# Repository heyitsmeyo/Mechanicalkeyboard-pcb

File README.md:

# Mechanicalkeyboard-pcb
a pcb design for a mechanical keyboard based on RP2040 MCU 

# if you like the project , you can donate us for more : 

    https://ko-fi.com/heyitsmeyo

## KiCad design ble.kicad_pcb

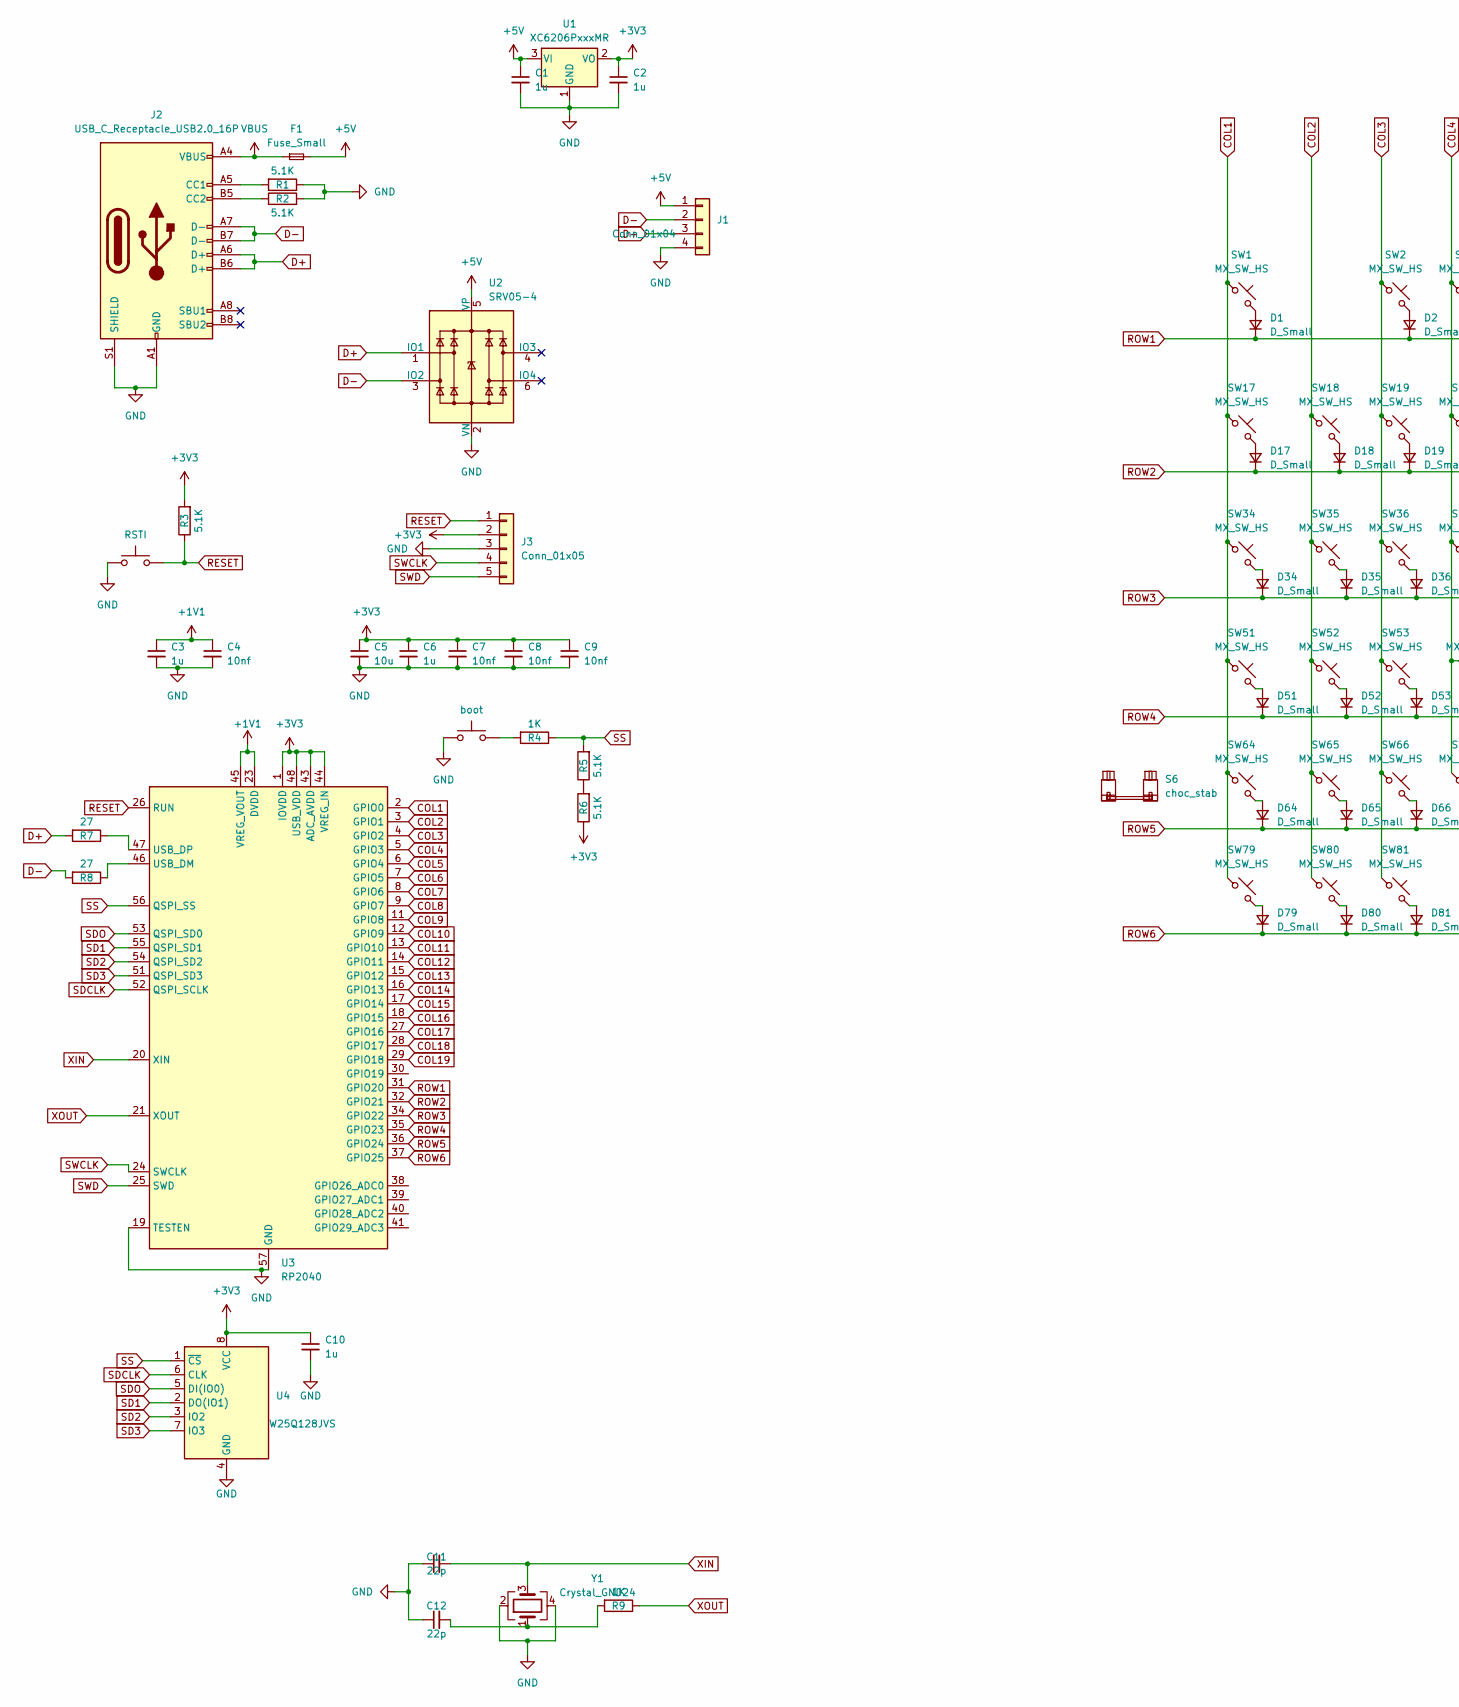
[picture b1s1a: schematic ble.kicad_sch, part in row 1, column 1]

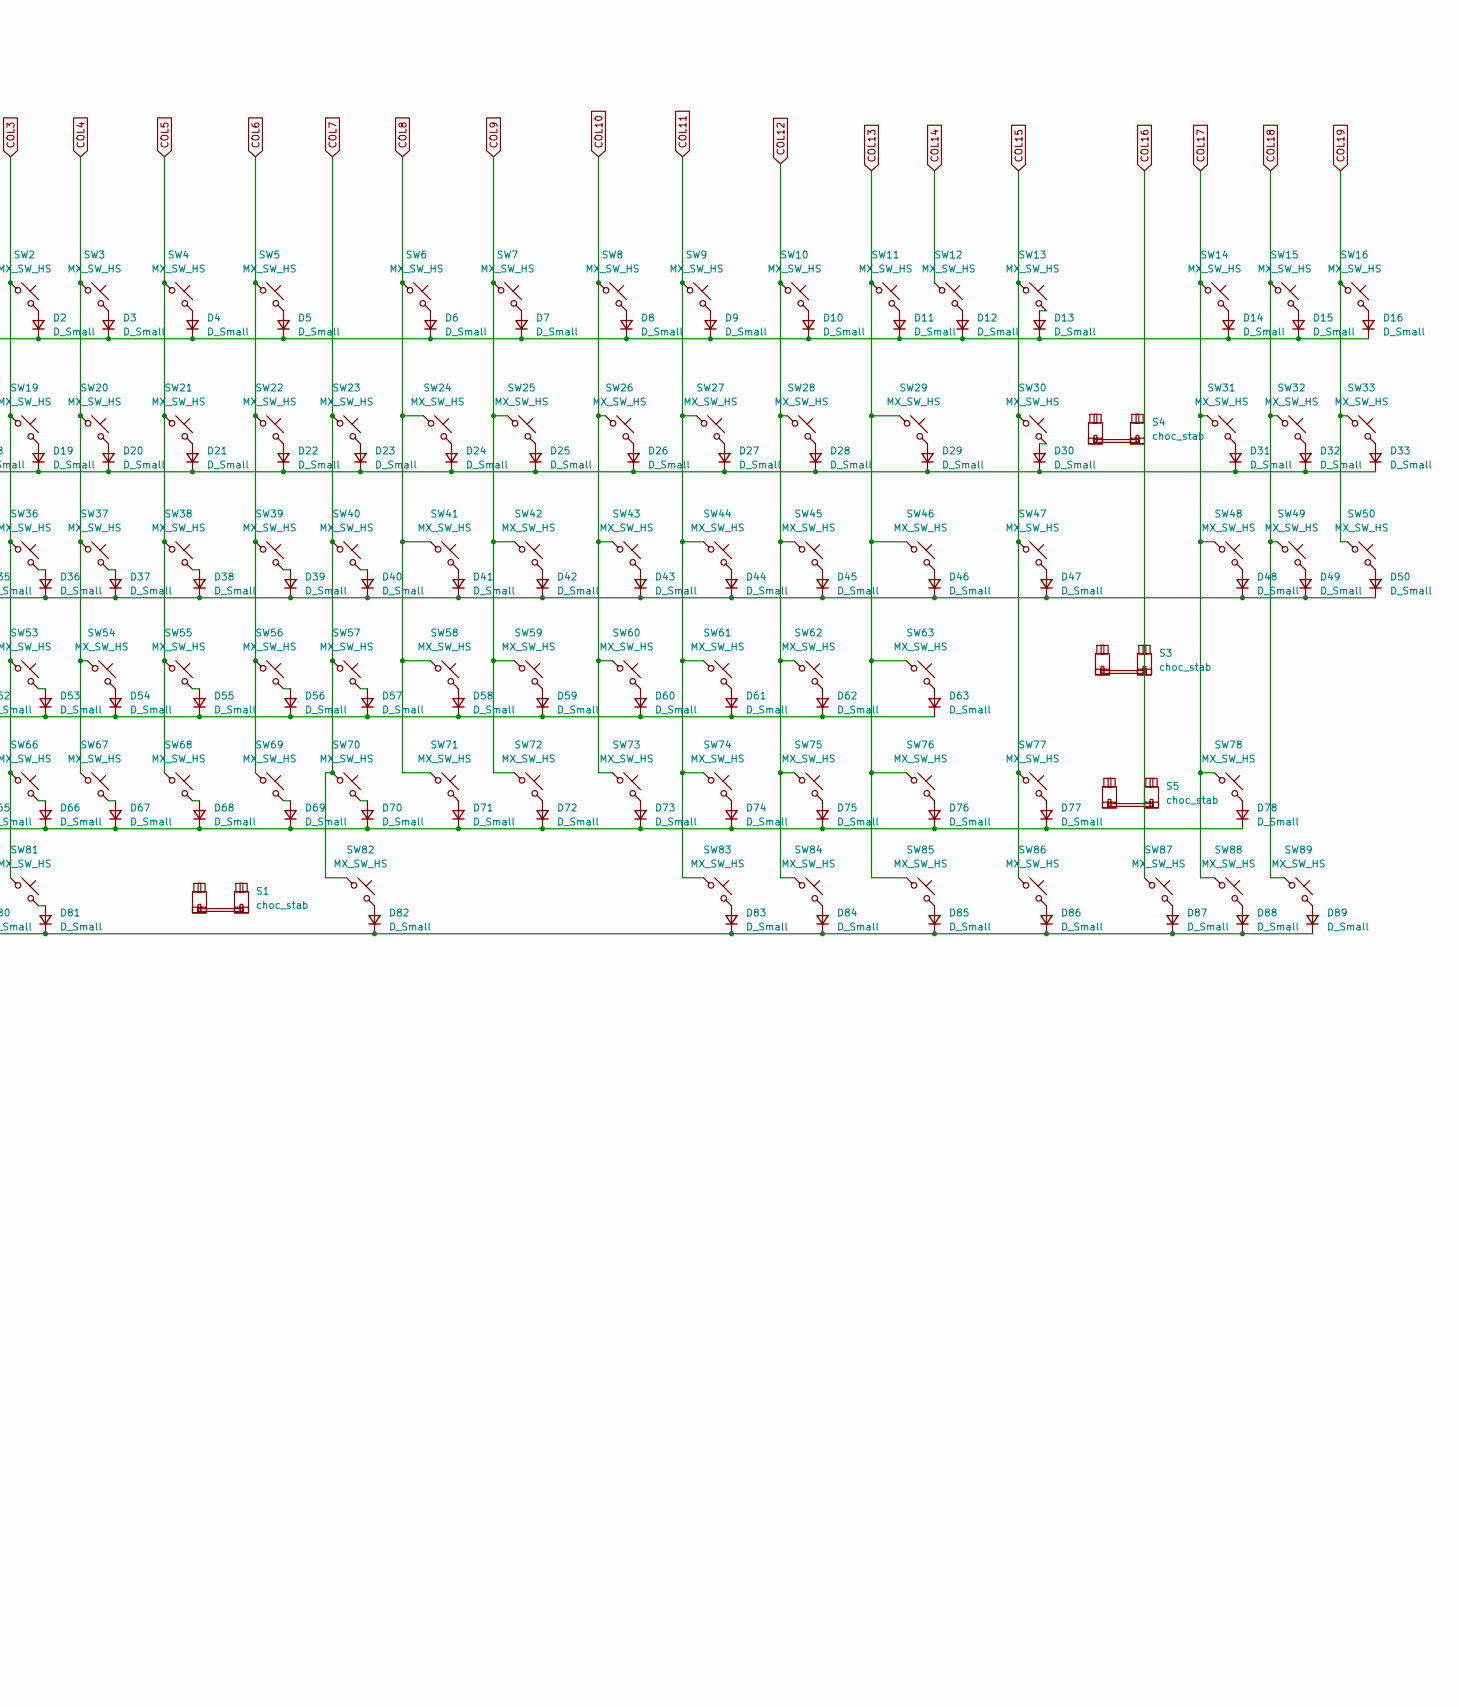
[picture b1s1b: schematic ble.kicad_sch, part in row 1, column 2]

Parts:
C1, C2, C3, C6, C10: 1u; C_0402_1005Metric
C4, C7, C8, C9: 10nf; C_0402_1005Metric
C5: 10u; C_0603_1608Metric
C11, C12: 22p; C_0402_1005Metric
D1, D2, D3, D4, D5, D6, D7, D8, D9, D10, D11, D12, D13, D14, D15, D16, D17, D18, D19, D20, D21, D22, D23, D24, D25, D26, D27, D28, D29, D30, D31, D32, D33, D34, D35, D36, D37, D38, D39, D40, D41, D42, D43, D44, D45, D46, D47, D48, D49, D50, D51, D52, D53, D54, D55, D56, D57, D58, D59, D60, D61, D62, D63, D64, D65, D66, D67, D68, D69, D70, D71, D72, D73, D74, D75, D76, D77, D78, D79, D80, D81, D82, D83, D84, D85, D86, D87, D88, D89: D_Small; D_SOD-123
F1: Fuse_Small; Fuse_1206_3216Metric
J1: Conn_01x04; JST_SH_SM04B-SRSS-TB_1x04-1MP_P1.00mm_Horizontal
J2: USB_C_Receptacle_USB2.0_16P; USB_C_Receptacle_HRO_TYPE-C-31-M-12
J3: Conn_01x05; PinHeader_1x05_P2.54mm_Vertical
R1, R2, R3, R5, R6: 5.1K; R_0402_1005Metric
R4, R9: 1K; R_0402_1005Metric
R7, R8: 27; R_0402_1005Metric
S1: choc_stab; STAB_MX_7u
S3: choc_stab; STAB_MX_ISO-ROT
S4, S6: choc_stab; STAB_choc_2u
S5: choc_stab; STAB_MX_2.25u
SW1, SW2, SW3, SW4, SW5, SW6, SW7, SW8, SW9, SW10, SW11, SW12, SW13, SW14, SW15, SW16, SW17, SW18, SW19, SW20, SW21, SW22, SW23, SW24, SW25, SW26, SW27, SW28, SW29, SW31, SW32, SW33, SW35, SW36, SW37, SW38, SW39, SW40, SW41, SW42, SW43, SW44, SW45, SW46, SW47, SW48, SW49, SW50, SW52, SW53, SW54, SW55, SW56, SW57, SW58, SW59, SW60, SW61, SW62, SW63, SW65, SW66, SW67, SW68, SW69, SW70, SW71, SW72, SW73, SW74, SW75, SW76, SW77, SW78, SW82, SW87: MX_SW_HS; SW_MX_HS_CPG151101S11_1u
SW30, SW34: MX_SW_HS; SW_MX_HS_CPG151101S11_1.5u
SW51: MX_SW_HS; SW_MX_HS_CPG151101S11_1.75u
SW64, SW79, SW80, SW81, SW83, SW84, SW85, SW86, SW88, SW89: MX_SW_HS; SW_MX_HS_CPG151101S11_1.25u
U1: XC6206PxxxMR; SOT-23-3
U2: SRV05-4; SOT-23-6
U3: RP2040; QFN-56-1EP_7x7mm_P0.4mm_EP3.2x3.2mm
U4: W25Q128JVS; SOIC-8_5.23x5.23mm_P1.27mm
Y1: Crystal_GND24; Crystal_SMD_3225-4Pin_3.2x2.5mm
k1: RSTI; SW_SPST_TL3342
k2: boot; SW_SPST_TL3342

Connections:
+1V1: C3.1, C4.1, U3.23 (DVDD), U3.45 (VREG_VOUT), U3.50 (DVDD)
+3V3: C2.1, C5.1, C6.1, C7.1, C8.1, C9.1, C10.1, J3.2, R3.2, R6.1, U1.2 (VO), U3.1 (IOVDD), U3.10 (IOVDD), U3.22 (IOVDD), U3.33 (IOVDD), U3.42 (IOVDD), U3.43 (ADC_AVDD), U3.44 (VREG_IN), U3.48 (USB_VDD), U3.49 (IOVDD), U4.8 (VCC)
+5V: C1.1, F1.2, J1.1, U1.3 (VI), U2.5 (VP)
COL4: SW3.1, SW20.1, SW37.1, SW54.1, SW67.1, U3.5 (GPIO3)
COL5: SW4.1, SW21.1, SW38.1, SW55.1, SW68.1, U3.6 (GPIO4)
COL6: SW5.1, SW22.1, SW39.1, SW56.1, SW69.1, U3.7 (GPIO5)
COL7: SW23.1, SW40.1, SW57.1, SW70.1, SW82.1, U3.8 (GPIO6)
COL8: SW6.1, SW24.1, SW41.1, SW58.1, SW71.1, U3.9 (GPIO7)
COL9: SW7.1, SW25.1, SW42.1, SW59.1, SW72.1, U3.11 (GPIO8)
COL10: SW8.1, SW26.1, SW43.1, SW60.1, SW73.1, U3.12 (GPIO9)
COL11: SW9.1, SW27.1, SW44.1, SW61.1, SW74.1, SW83.1, U3.13 (GPIO10)
COL12: SW10.1, SW28.1, SW45.1, SW62.1, SW75.1, SW84.1, U3.14 (GPIO11)
COL14: SW12.1, U3.16 (GPIO13)
COL15: SW13.1, SW30.1, SW47.1, SW77.1, SW86.1, U3.17 (GPIO14)
COL16: SW87.1, U3.18 (GPIO15)
COL17: SW14.1, SW31.1, SW48.1, SW78.1, SW88.1, U3.27 (GPIO16)
COL19: SW16.1, SW33.1, SW50.1, U3.29 (GPIO18)
D+: J1.3, J2.A6 (D+), J2.B6 (D+), R7.2, U2.1 (IO1)
D-: J1.2, J2.A7 (D-), J2.B7 (D-), R8.2, U2.3 (IO2)
GND: C1.2, C2.2, C3.2, C4.2, C5.2, C6.2, C7.2, C8.2, C9.2, C10.2, C11.1, C12.1, J1.4, J2.A1 (GND), J2.A12 (GND), J2.B1 (GND), J2.B12 (GND), J2.S1 (SHIELD), J3.3, R1.1, R2.2, U1.1 (GND), U2.2 (VN), U3.19 (TESTEN), U3.57 (GND), U4.4 (GND), Y1.2, Y1.4, k1.1, k2.1
unnamed: C12.2, R9.2, Y1.1
unnamed: D1.2 (A), SW1.2
unnamed: D2.2 (A), SW2.2
unnamed: D3.2 (A), SW3.2
unnamed: D4.2 (A), SW4.2
unnamed: D5.2 (A), SW5.2
unnamed: D6.2 (A), SW6.2
unnamed: D7.2 (A), SW7.2
unnamed: D8.2 (A), SW8.2
unnamed: D9.2 (A), SW9.2
unnamed: D10.2 (A), SW10.2
unnamed: D11.2 (A), SW11.2
unnamed: D12.2 (A), SW12.2
unnamed: D13.2 (A), SW13.2
unnamed: D14.2 (A), SW14.2
unnamed: D15.2 (A), SW15.2
unnamed: D16.2 (A), SW16.2
unnamed: D17.2 (A), SW17.2
unnamed: D18.2 (A), SW18.2
unnamed: D19.2 (A), SW19.2
unnamed: D20.2 (A), SW20.2
unnamed: D21.2 (A), SW21.2
unnamed: D22.2 (A), SW22.2
unnamed: D23.2 (A), SW23.2
unnamed: D24.2 (A), SW24.2
unnamed: D25.2 (A), SW25.2
unnamed: D26.2 (A), SW26.2
unnamed: D27.2 (A), SW27.2
unnamed: D28.2 (A), SW28.2
unnamed: D29.2 (A), SW29.2
unnamed: D30.2 (A), SW30.2
unnamed: D31.2 (A), SW31.2
unnamed: D32.2 (A), SW32.2
unnamed: D33.2 (A), SW33.2
unnamed: D34.2 (A), SW34.2
unnamed: D35.2 (A), SW35.2
unnamed: D36.2 (A), SW36.2
unnamed: D37.2 (A), SW37.2
unnamed: D38.2 (A), SW38.2
unnamed: D39.2 (A), SW39.2
unnamed: D40.2 (A), SW40.2
unnamed: D41.2 (A), SW41.2
unnamed: D42.2 (A), SW42.2
unnamed: D43.2 (A), SW43.2
unnamed: D44.2 (A), SW44.2
unnamed: D45.2 (A), SW45.2
unnamed: D46.2 (A), SW46.2
unnamed: D47.2 (A), SW47.2
unnamed: D48.2 (A), SW48.2
unnamed: D49.2 (A), SW49.2
unnamed: D50.2 (A), SW50.2
unnamed: D51.2 (A), SW51.2
unnamed: D52.2 (A), SW52.2
unnamed: D53.2 (A), SW53.2
unnamed: D54.2 (A), SW54.2
unnamed: D55.2 (A), SW55.2
unnamed: D56.2 (A), SW56.2
unnamed: D57.2 (A), SW57.2
unnamed: D58.2 (A), SW58.2
unnamed: D59.2 (A), SW59.2
unnamed: D60.2 (A), SW60.2
unnamed: D61.2 (A), SW61.2
unnamed: D62.2 (A), SW62.2
unnamed: D63.2 (A), SW63.2
unnamed: D64.2 (A), SW64.2
unnamed: D65.2 (A), SW65.2
unnamed: D66.2 (A), SW66.2
unnamed: D67.2 (A), SW67.2
unnamed: D68.2 (A), SW68.2
unnamed: D69.2 (A), SW69.2
unnamed: D70.2 (A), SW70.2
unnamed: D71.2 (A), SW71.2
unnamed: D72.2 (A), SW72.2
unnamed: D73.2 (A), SW73.2
unnamed: D74.2 (A), SW74.2
unnamed: D75.2 (A), SW75.2
unnamed: D76.2 (A), SW76.2
unnamed: D77.2 (A), SW77.2
unnamed: D78.2 (A), SW78.2
unnamed: D79.2 (A), SW79.2
unnamed: D80.2 (A), SW80.2
unnamed: D81.2 (A), SW81.2
unnamed 102: D82.2 (A), SW82.2; also elsewhere on the board
unnamed: D83.2 (A), SW83.2
unnamed: D84.2 (A), SW84.2
unnamed: D85.2 (A), SW85.2
unnamed: D86.2 (A), SW86.2
unnamed: D87.2 (A), SW87.2
unnamed: D88.2 (A), SW88.2
unnamed: D89.2 (A), SW89.2
unnamed: J2.A5 (CC1), R1.2
unnamed: J2.B5 (CC2), R2.1
unnamed: R4.2, k2.2
unnamed: R5.1, R6.2
unnamed: R8.1, U3.46 (USB_DM)
unnamed: R7.1, U3.47 (USB_DP)
RESET: J3.1, R3.1, U3.26 (RUN), k1.2
ROW1: D1.1 (K), D2.1 (K), D3.1 (K), D4.1 (K), D5.1 (K), D6.1 (K), D7.1 (K), D8.1 (K), D9.1 (K), D10.1 (K), D11.1 (K), D12.1 (K), D13.1 (K), D14.1 (K), D15.1 (K), D16.1 (K), U3.31 (GPIO20)
ROW2: D17.1 (K), D18.1 (K), D19.1 (K), D20.1 (K), D21.1 (K), D22.1 (K), D23.1 (K), D24.1 (K), D25.1 (K), D26.1 (K), D27.1 (K), D28.1 (K), D29.1 (K), D30.1 (K), D31.1 (K), D32.1 (K), D33.1 (K), U3.32 (GPIO21)
ROW3: D34.1 (K), D35.1 (K), D36.1 (K), D37.1 (K), D38.1 (K), D39.1 (K), D40.1 (K), D41.1 (K), D42.1 (K), D43.1 (K), D44.1 (K), D45.1 (K), D46.1 (K), D47.1 (K), D48.1 (K), D49.1 (K), D50.1 (K), U3.34 (GPIO22)
SD1: U3.55 (QSPI_SD1), U4.2 (DO(IO1))
SD2: U3.54 (QSPI_SD2), U4.3 (IO2)
SD3: U3.51 (QSPI_SD3), U4.7 (IO3)
SDCLK: U3.52 (QSPI_SCLK), U4.6 (CLK)
SDO: U3.53 (QSPI_SD0), U4.5 (DI(IO0))
SS: R4.1, R5.2, U3.56 (QSPI_SS), U4.1 (~CS)
SWCLK: J3.4, U3.24 (SWCLK)
SWD: J3.5, U3.25 (SWD)
VBUS: F1.1, J2.A4 (VBUS), J2.A9 (VBUS), J2.B4 (VBUS), J2.B9 (VBUS)
XIN: C11.2, U3.20 (XIN), Y1.3
XOUT: R9.1, U3.21 (XOUT)

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
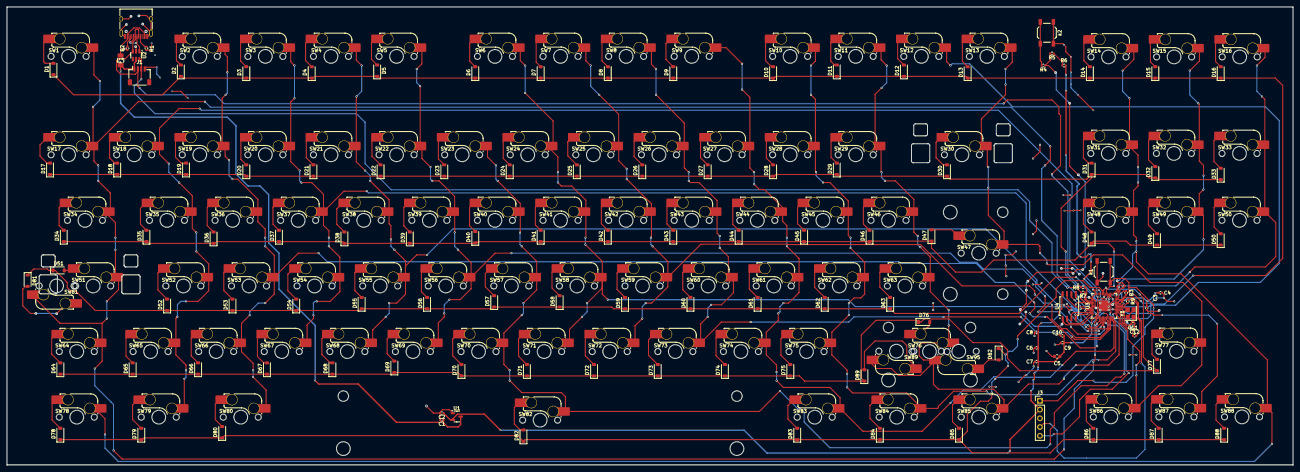
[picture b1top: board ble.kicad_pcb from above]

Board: 4 copper layers, 373.4 x 132.9 mm, 217 parts (0 on the bottom side), 139 nets.

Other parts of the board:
D82#2: D_Small; D_SOD-123
SW95: MX_SW_HS; SW_MX_HS_CPG151101S11_1u

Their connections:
unnamed 102: D82#2.2 (A), SW95.2; also elsewhere on the board
